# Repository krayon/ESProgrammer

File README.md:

# ESProgrammer
ESP8266 programming board

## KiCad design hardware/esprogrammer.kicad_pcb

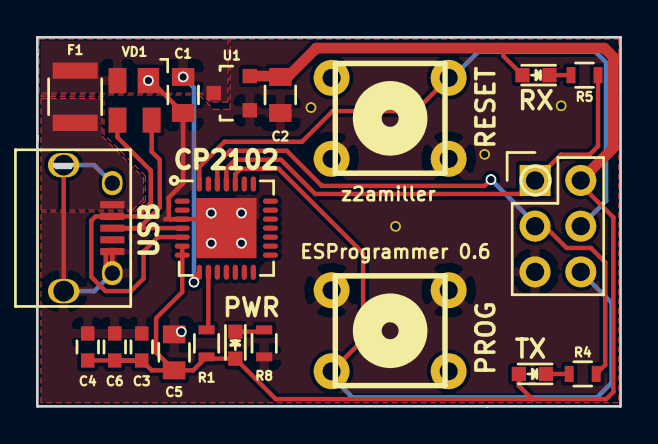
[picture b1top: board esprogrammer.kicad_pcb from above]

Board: 2 copper layers, 32.4 x 20.5 mm, 21 parts (0 on the bottom side), 14 nets.

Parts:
C1, C2: 10uF; C_0805
C3, C6: 100nF; C_0603
C4: 1uF; C_0603
C5: 4.7uF; C_0805
D1: Led_Red; LED_0603
D2: Led_Yellow; LED_0603
D5: Led_Amber; LED_0603
F1: 500mA; R_1210
P1: USB_OTG; USB_Micro-B
P2: CONN_02X03; Pin_Header_Straight_2x03
R1: 10k; R_0603
R4, R5, R8: 220; R_0603
SW1, SW2: SW_PUSH; PCB_PUSH
U1: AP1117; SOT-23
U2: CP2102; QFN-28-1EP_5x5mm_Pitch0.5mm
VD1: SP0503BAHTG; SOT-143

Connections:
+3V3: C2.1, C3.1, C4.1, C5.1, C6.1, D1.2, D2.2, D5.2, P2.2, R1.1, U1.2, U2.6, U2.7
+5V: C1.1, F1.2, U1.3, U2.8, VD1.2
D+: P1.3, U2.4, VD1.4
D-: P1.2, U2.5, VD1.3
DTR: P2.4, SW1.1, U2.28
ESP_RST: P2.6, SW2.1, U2.24
GND: C1.2, C2.2, C3.2, C4.2, C5.2, C6.2, P1.5, P1.6, P2.5, R8.2, SW1.2, SW1.4, SW2.2, SW2.4, U1.1, U2.3, U2.29, VD1.1
unnamed: D1.1, R4.1
unnamed: D2.1, R5.1
unnamed: D5.1, R8.1
unnamed: F1.1, P1.1
unnamed: R1.2, U2.9
RXD: P2.1, R5.2, U2.25
TXD: P2.3, R4.2, U2.26

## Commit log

2016-06-18 Initial commit of ESP Programmer board.
2016-07-04 Re-center some parts, bigger 3v3 traces.
2016-07-04 Update silkscreened version.
2016-07-05 Fix 3v3 fill, add some gnd vias.
2016-07-05 Improve via placement.
2016-07-06 Shrink board for v0.5
2016-07-09 Programmer 0.6 - cleanup and use reflow size pads.
